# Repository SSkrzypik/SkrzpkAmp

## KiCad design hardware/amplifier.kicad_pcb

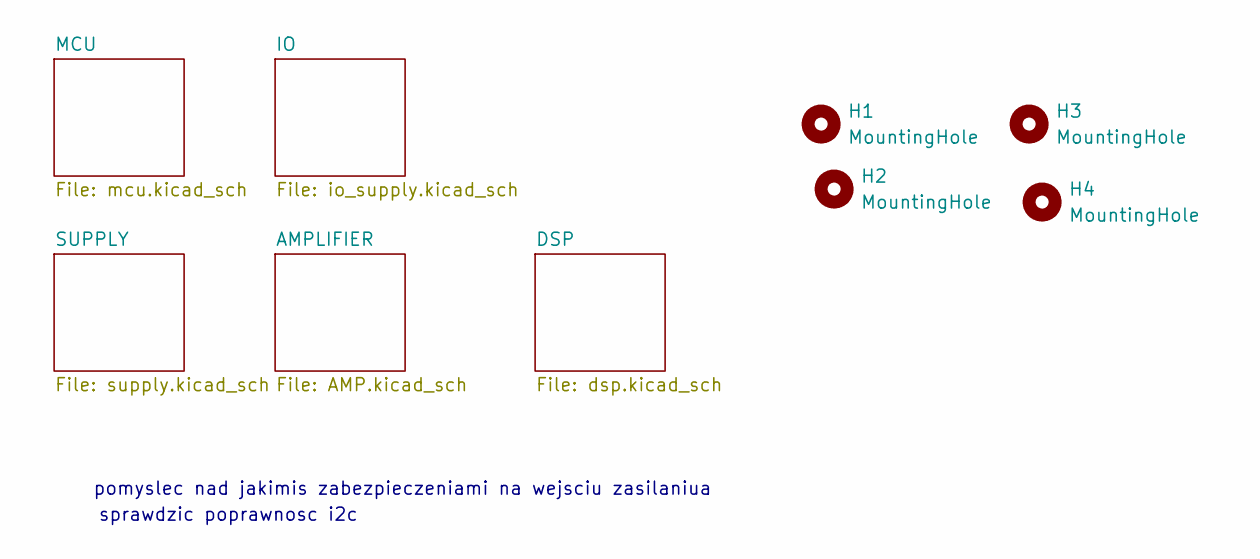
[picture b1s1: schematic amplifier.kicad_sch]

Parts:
H1, H2, H3, H4: MountingHole; MountingHole_3.2mm_M3

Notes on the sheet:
sprawdzic poprawnosc i2c
pomyslec nad jakimis zabezpieczeniami na wejsciu zasilaniua

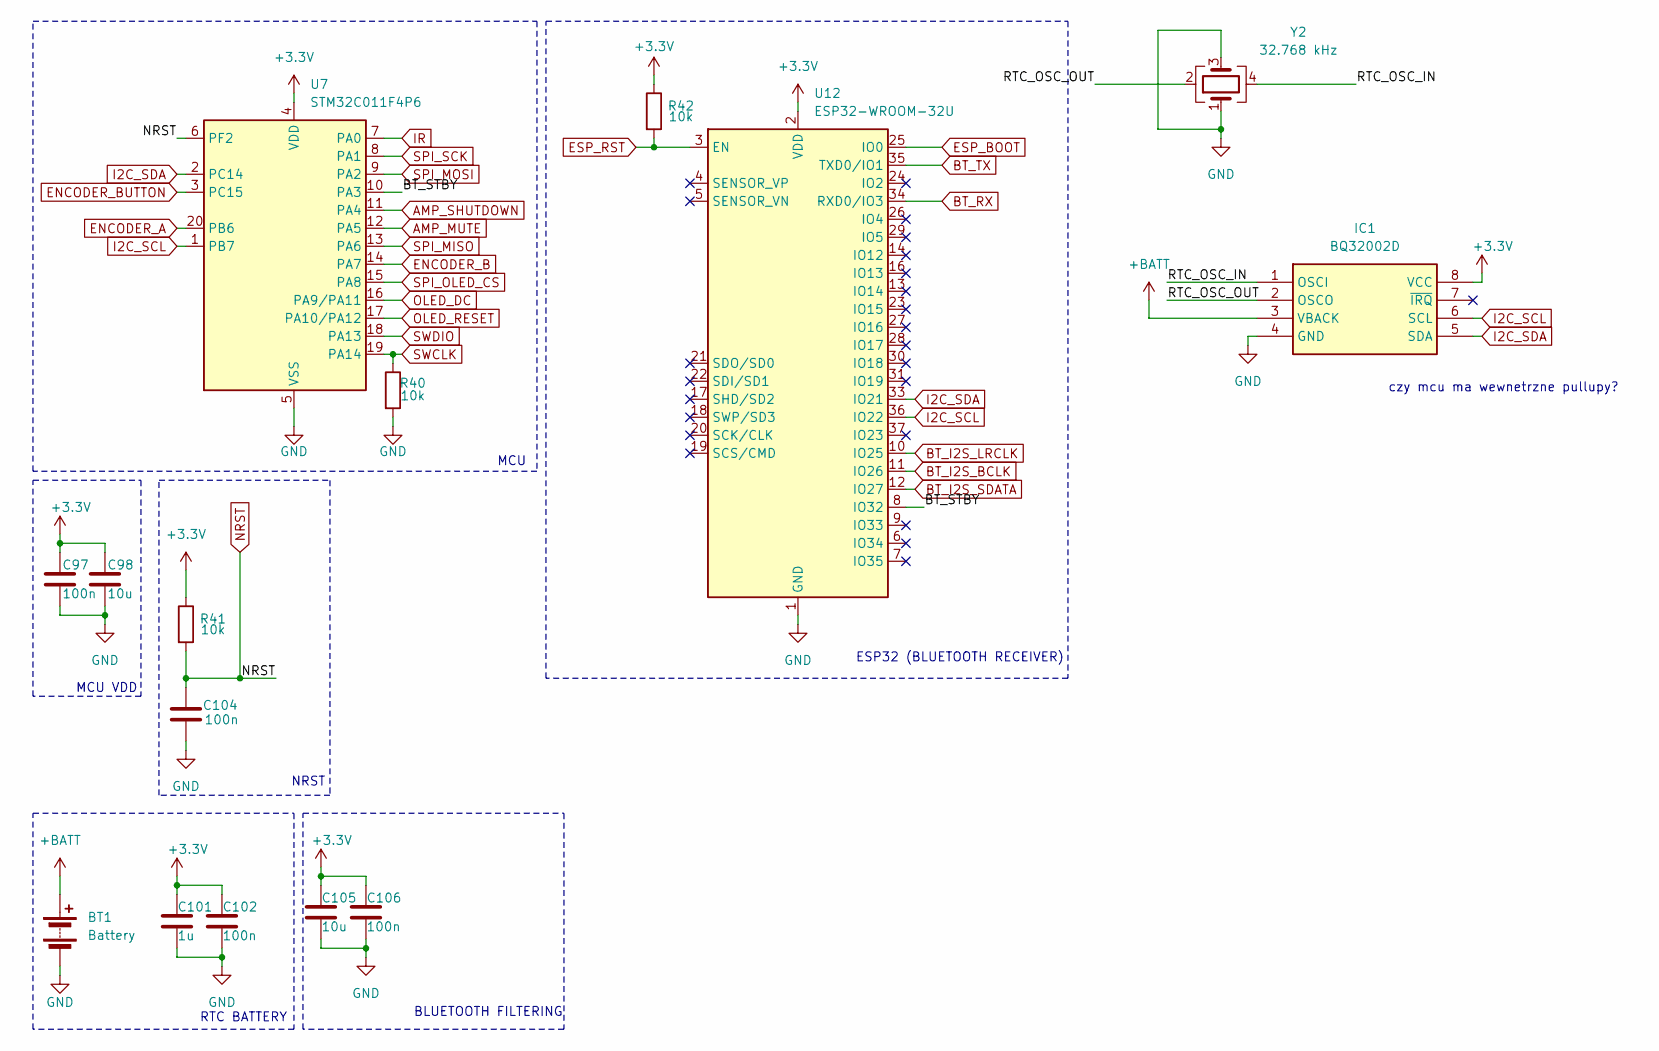
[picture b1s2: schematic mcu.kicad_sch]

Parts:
BT1: Battery; BatteryHolder_LINX_BAT-HLD-012-SMT
C97, C102, C104, C106: 100n; C_0603_1608Metric_Pad1.08x0.95mm_HandSolder
C98, C105: 10u; C_0603_1608Metric_Pad1.08x0.95mm_HandSolder
C101: 1u; C_0603_1608Metric_Pad1.08x0.95mm_HandSolder
IC1: BQ32002D; Mouser Part Number 595-BQ32002D
R40, R41, R42: 10k; R_0603_1608Metric_Pad0.98x0.95mm_HandSolder
U7: STM32C011F4P6; TSSOP-20_4.4x6.5mm_P0.65mm
U12: ESP32-WROOM-32U
Y2: 32.768 kHz; 32768K125PIMC306

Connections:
+BATT: BT1.1 (+), IC1.3 (VBACK)
/MCU/BT_STBY: U7.10 (PA3), U12.8 (IO32)
/MCU/RTC_OSC_IN: IC1.1 (OSCI), Y2.4
/MCU/RTC_OSC_OUT: IC1.2 (OSCO), Y2.2
AMP_MUTE: U7.12 (PA5); also elsewhere on the board
AMP_SHUTDOWN: U7.11 (PA4); also elsewhere on the board
BT_I2S_BCLK: U12.11 (IO26); also elsewhere on the board
BT_I2S_LRCLK: U12.10 (IO25); also elsewhere on the board
BT_I2S_SDATA: U12.12 (IO27); also elsewhere on the board
BT_RX: U12.34 (RXD0/IO3); also elsewhere on the board
BT_TX: U12.35 (TXD0/IO1); also elsewhere on the board
ENCODER_A: U7.20 (PB6); also elsewhere on the board
ENCODER_B: U7.14 (PA7); also elsewhere on the board
ENCODER_BUTTON: U7.3 (PC15); also elsewhere on the board
ESP_BOOT: U12.25 (IO0); also elsewhere on the board
ESP_RST: R42.2, U12.3 (EN); also elsewhere on the board
I2C_SCL: IC1.6 (SCL), U7.1 (PB7), U12.36 (IO22); also elsewhere on the board
I2C_SDA: IC1.5 (SDA), U7.2 (PC14), U12.33 (IO21); also elsewhere on the board
IR: U7.7 (PA0); also elsewhere on the board
NRST: C104.1, R41.2, U7.6 (PF2); also elsewhere on the board
OLED_DC: U7.16 (PA9/PA11); also elsewhere on the board
OLED_RESET: U7.17 (PA10/PA12); also elsewhere on the board
SPI_MISO: U7.13 (PA6); also elsewhere on the board
SPI_MOSI: U7.9 (PA2); also elsewhere on the board
SPI_OLED_CS: U7.15 (PA8); also elsewhere on the board
SPI_SCK: U7.8 (PA1); also elsewhere on the board
SWCLK: R40.1, U7.19 (PA14); also elsewhere on the board
SWDIO: U7.18 (PA13); also elsewhere on the board

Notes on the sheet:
MCU
ESP32 (BLUETOOTH RECEIVER)
czy mcu ma wewnetrzne pullupy?
RTC BATTERY
NRST
MCU VDD
BLUETOOTH FILTERING

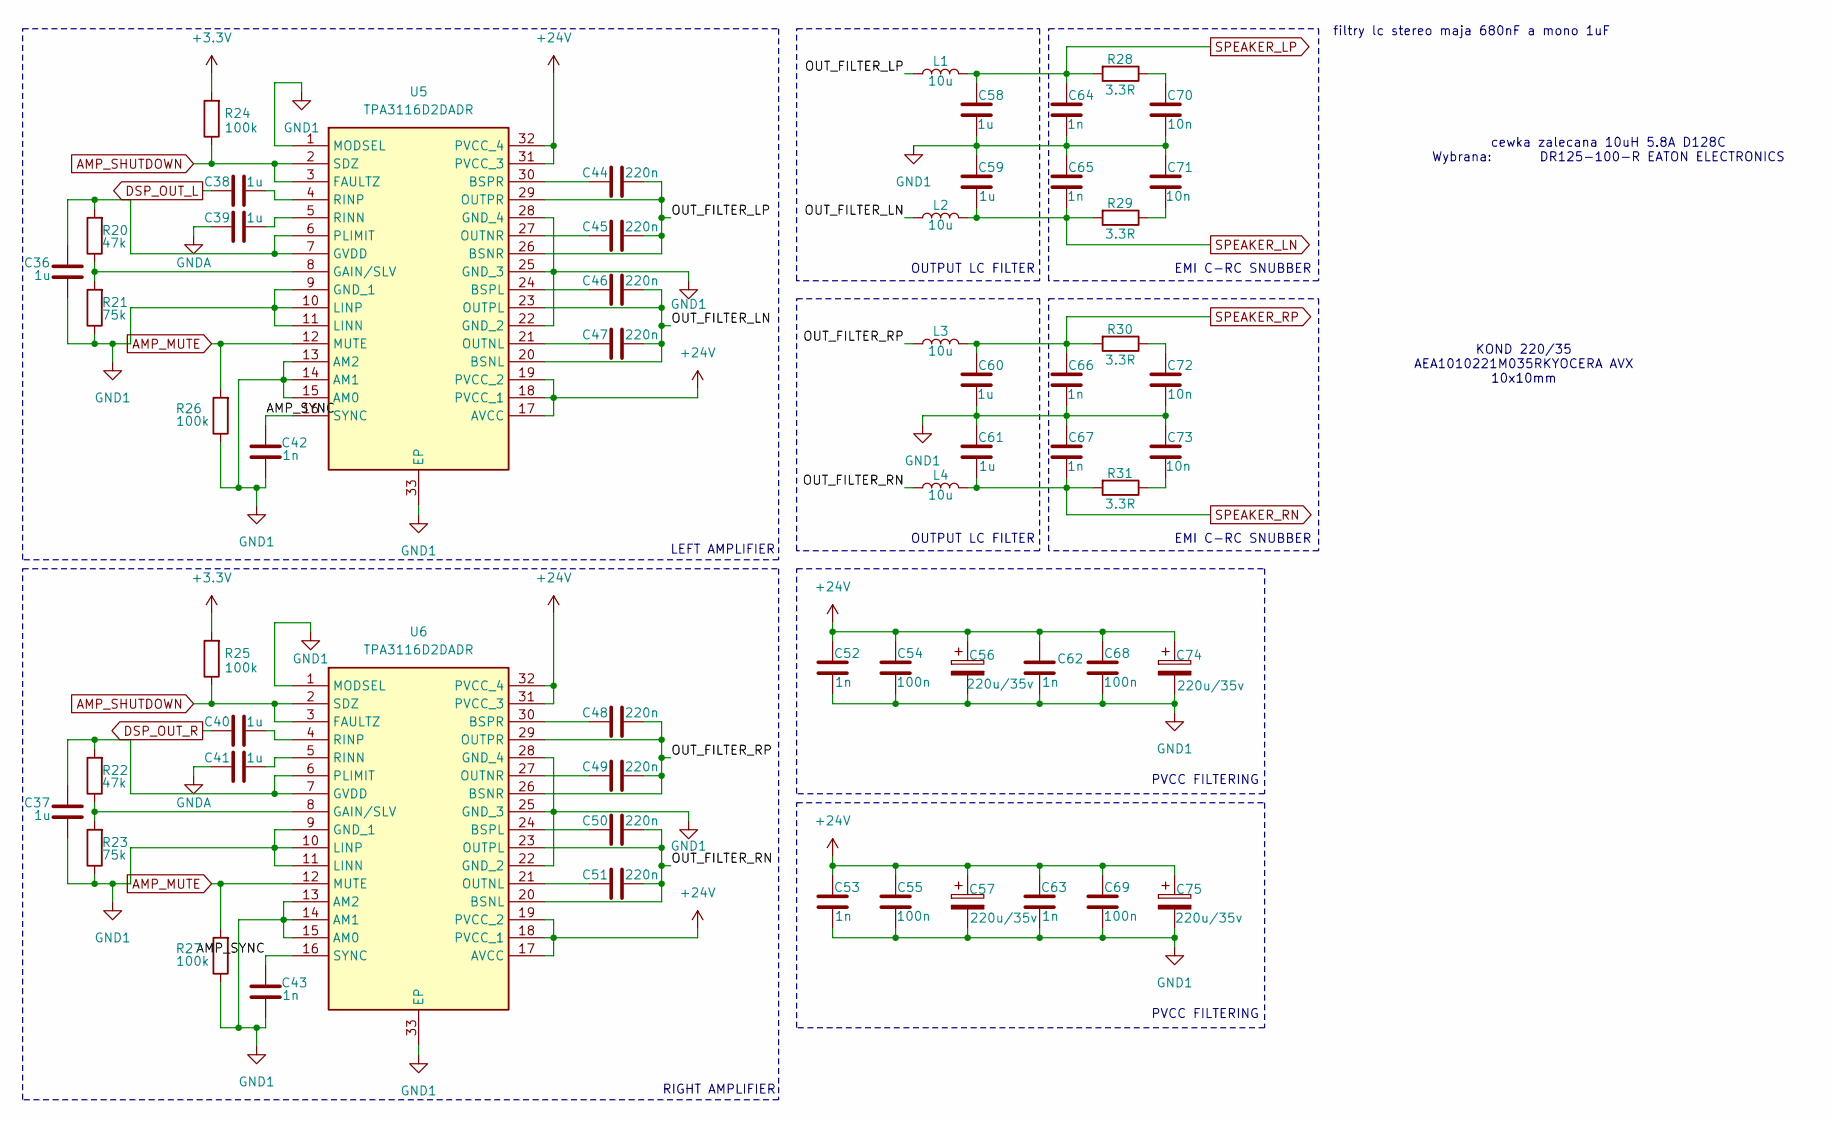
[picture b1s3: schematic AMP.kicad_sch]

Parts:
C36, C37, C38, C39, C40, C41, C58, C59, C60, C61: 1u; C_0603_1608Metric_Pad1.08x0.95mm_HandSolder
C42, C43, C52, C53, C62, C63, C64, C65, C66, C67: 1n; C_0603_1608Metric_Pad1.08x0.95mm_HandSolder
C44, C45, C46, C47, C48, C49, C50, C51: 220n; C_0603_1608Metric_Pad1.08x0.95mm_HandSolder
C54, C55, C68, C69: 100n; C_0603_1608Metric_Pad1.08x0.95mm_HandSolder
C56, C57, C74, C75: 220u/35v; CP_Elec_10x10
C70, C71, C72, C73: 10n; C_0603_1608Metric_Pad1.08x0.95mm_HandSolder
L1, L2, L3, L4: 10u; DR127-100-R
R20, R22: 47k; R_0603_1608Metric_Pad0.98x0.95mm_HandSolder
R21, R23: 75k; R_0603_1608Metric_Pad0.98x0.95mm_HandSolder
R24, R25, R26, R27: 100k; R_0603_1608Metric_Pad0.98x0.95mm_HandSolder
R28, R29, R30, R31: 3.3R; R_0603_1608Metric_Pad0.98x0.95mm_HandSolder
U5, U6: TPA3116D2DADR; SOP65P810X120-33N; Manufacturer_Part_Number TPA3116D2DADR

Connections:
/AMPLIFIER/AMP_SYNC: C42.1, C43.1, U5.16 (SYNC), U6.16 (SYNC)
/AMPLIFIER/OUT_FILTER_LN: C46.1, C47.1, L2.1, U5.20 (BSNL), U5.23 (OUTPL)
/AMPLIFIER/OUT_FILTER_LP: C44.1, C45.1, L1.1, U5.26 (BSNR), U5.29 (OUTPR)
/AMPLIFIER/OUT_FILTER_RN: C50.1, C51.1, L4.1, U6.20 (BSNL), U6.23 (OUTPL)
/AMPLIFIER/OUT_FILTER_RP: C48.1, C49.1, L3.1, U6.26 (BSNR), U6.29 (OUTPR)
AMP_MUTE: R26.2, R27.2, U5.12 (MUTE), U6.12 (MUTE); also elsewhere on the board
AMP_SHUTDOWN: R24.1, R25.1, U5.2 (SDZ), U5.3 (FAULTZ), U6.2 (SDZ), U6.3 (FAULTZ); also elsewhere on the board
DSP_OUT_L: C38.2; also elsewhere on the board
DSP_OUT_R: C40.2; also elsewhere on the board
GND1: C36.2, C37.2, C42.2, C43.2, C52.2, C53.2, C54.2, C55.2, C56.2, C57.2, C58.2, C59.1, C60.2, C61.1, C62.2, C63.2, C64.2, C65.1, C66.2, C67.1, C68.2, C69.2, C70.2, C71.1, C72.2, C73.1, C74.2, C75.2, R21.1, R23.1, R26.1, R27.1, U5.1 (MODSEL), U5.9 (GND_1), U5.10 (LINP), U5.11 (LINN), U5.13 (AM2), U5.14 (AM1), U5.15 (AM0), U5.22 (GND_2), U5.25 (GND_3), U5.28 (GND_4), U5.33 (EP), U6.1 (MODSEL), U6.9 (GND_1), U6.10 (LINP), U6.11 (LINN), U6.13 (AM2), U6.14 (AM1), U6.15 (AM0), U6.22 (GND_2), U6.25 (GND_3), U6.28 (GND_4), U6.33 (EP); also elsewhere on the board
unnamed: C70.1, R28.1
unnamed: C71.2, R29.1
unnamed: C72.1, R30.1
unnamed: C73.2, R31.1
unnamed: C46.2, U5.24 (BSPL)
unnamed: C44.2, U5.30 (BSPR)
unnamed: R20.1, R21.2, U5.8 (GAIN/SLV)
unnamed: C36.1, R20.2, U5.6 (PLIMIT), U5.7 (GVDD)
unnamed: C47.2, U5.21 (OUTNL)
unnamed: C45.2, U5.27 (OUTNR)
unnamed: C39.1, U5.5 (RINN)
unnamed: C38.1, U5.4 (RINP)
unnamed: C50.2, U6.24 (BSPL)
unnamed: C48.2, U6.30 (BSPR)
unnamed: R22.1, R23.2, U6.8 (GAIN/SLV)
unnamed: C37.1, R22.2, U6.6 (PLIMIT), U6.7 (GVDD)
unnamed: C51.2, U6.21 (OUTNL)
unnamed: C49.2, U6.27 (OUTNR)
unnamed: C41.1, U6.5 (RINN)
unnamed: C40.1, U6.4 (RINP)
SPEAKER_LN: C59.2, C65.2, L2.2, R29.2; also elsewhere on the board
SPEAKER_LP: C58.1, C64.1, L1.2, R28.2; also elsewhere on the board
SPEAKER_RN: C61.2, C67.2, L4.2, R31.2; also elsewhere on the board
SPEAKER_RP: C60.1, C66.1, L3.2, R30.2; also elsewhere on the board

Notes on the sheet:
PVCC FILTERING
EMI C-RC SNUBBER
RIGHT AMPLIFIER
filtry lc stereo maja 680nF a mono 1uF
OUTPUT LC FILTER
cewka zalecana 10uH 5.8A D128C Wybrana: DR125-100-R EATON ELECTRONICS
LEFT AMPLIFIER
KOND 220/35 AEA1010221M035RKYOCERA AVX 10x10mm

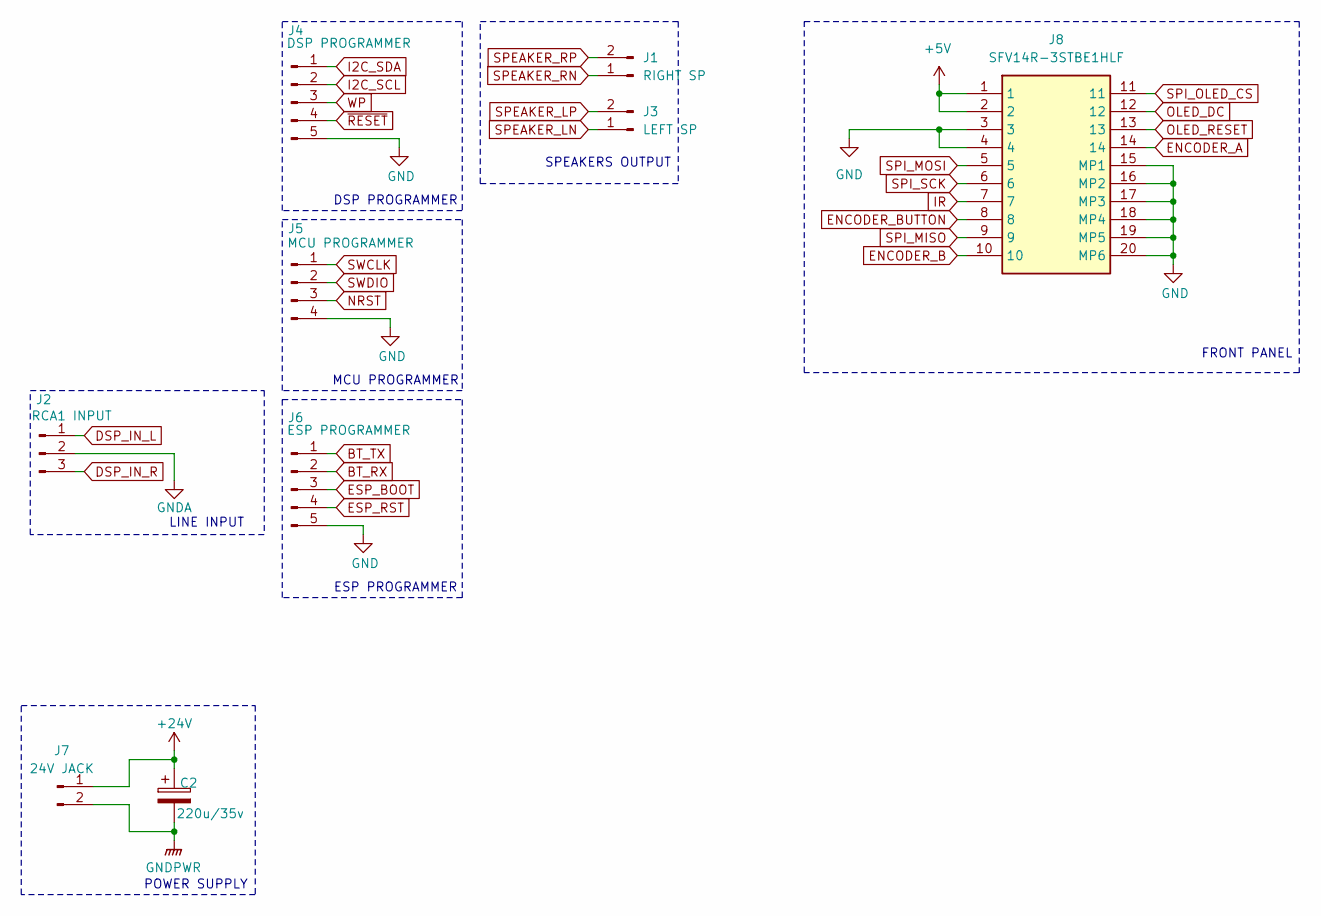
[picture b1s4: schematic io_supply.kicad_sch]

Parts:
C2: 220u/35v; CP_Elec_10x10
J1: RIGHT SP; 2828362
J2: RCA1 INPUT; JST_PH_B3B-PH-K_1x03_P2.00mm_Vertical
J3: LEFT SP; 2828362
J4: DSP PROGRAMMER; PinHeader_1x05_P2.54mm_Vertical
J5: MCU PROGRAMMER; PinHeader_1x04_P2.54mm_Vertical
J6: ESP PROGRAMMER; PinHeader_1x05_P2.54mm_Vertical
J7: 24V JACK; 2828362
J8: SFV14R-3STBE1HLF; SFV14R3STBE1HLF; Manufacturer_Part_Number SFV14R-3STBE1HLF

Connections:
BT_RX: J6.2; also elsewhere on the board
BT_TX: J6.1; also elsewhere on the board
DSP_IN_R: J2.3; also elsewhere on the board
ENCODER_A: J8.14; also elsewhere on the board
ENCODER_B: J8.10; also elsewhere on the board
ENCODER_BUTTON: J8.8; also elsewhere on the board
ESP_BOOT: J6.3; also elsewhere on the board
ESP_RST: J6.4; also elsewhere on the board
I2C_SCL: J4.2; also elsewhere on the board
I2C_SDA: J4.1; also elsewhere on the board
IR: J8.7; also elsewhere on the board
NRST: J5.3; also elsewhere on the board
OLED_DC: J8.12; also elsewhere on the board
OLED_RESET: J8.13; also elsewhere on the board
SPEAKER_LN: J3.1; also elsewhere on the board
SPEAKER_LP: J3.2; also elsewhere on the board
SPEAKER_RN: J1.1; also elsewhere on the board
SPEAKER_RP: J1.2; also elsewhere on the board
SPI_MISO: J8.9; also elsewhere on the board
SPI_MOSI: J8.5; also elsewhere on the board
SPI_OLED_CS: J8.11; also elsewhere on the board
SPI_SCK: J8.6; also elsewhere on the board
SWCLK: J5.1; also elsewhere on the board
SWDIO: J5.2; also elsewhere on the board
WP: J4.3; also elsewhere on the board
~RESET: J4.4; also elsewhere on the board

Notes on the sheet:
POWER SUPPLY
MCU PROGRAMMER
DSP PROGRAMMER
FRONT PANEL
SPEAKERS OUTPUT
LINE INPUT
ESP PROGRAMMER

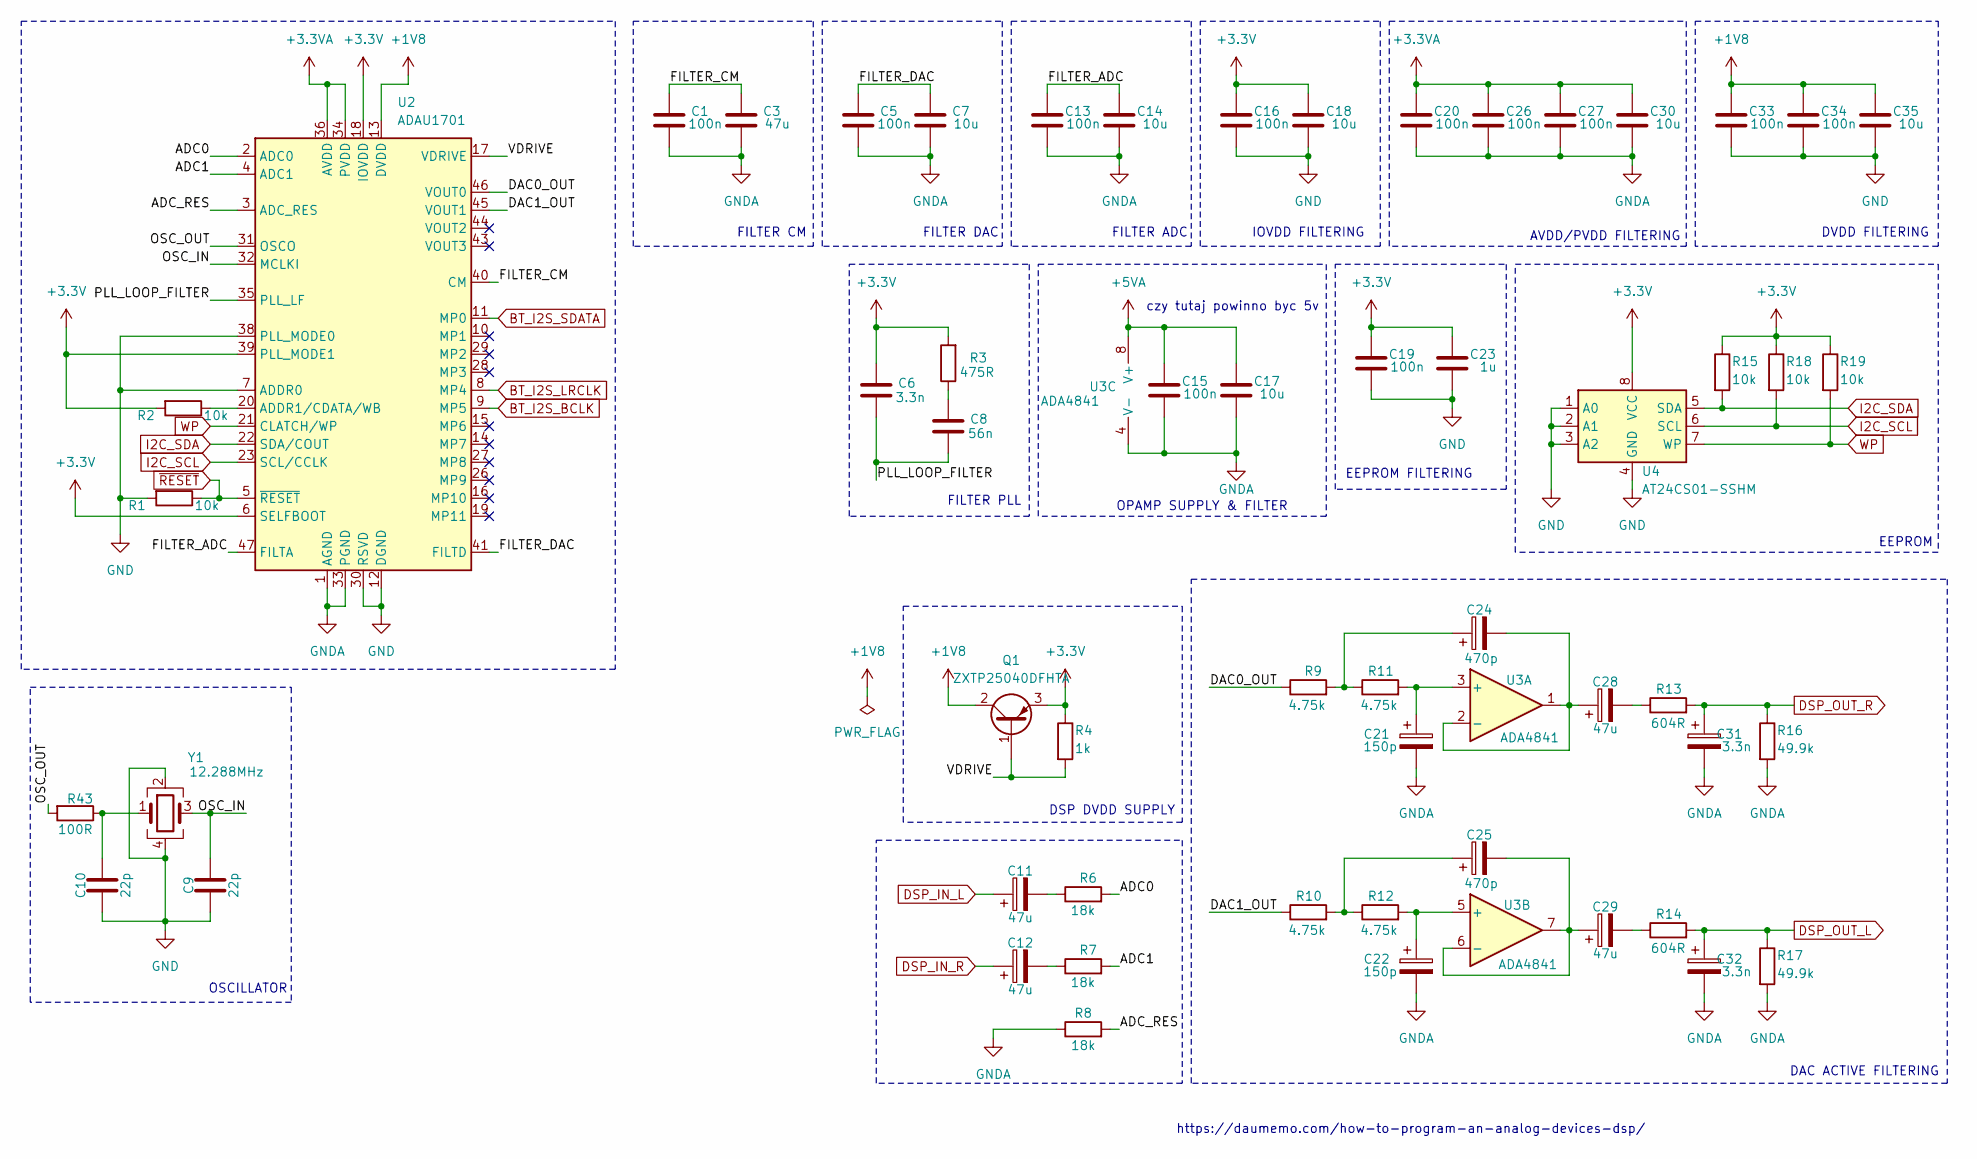
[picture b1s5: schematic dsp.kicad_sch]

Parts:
C1, C5, C13, C15, C16, C19, C20, C26, C27, C33, C34: 100n; C_0603_1608Metric_Pad1.08x0.95mm_HandSolder
C3, C11, C12, C28, C29: 47u; C_0603_1608Metric_Pad1.08x0.95mm_HandSolder
C6, C31, C32: 3.3n; C_0603_1608Metric_Pad1.08x0.95mm_HandSolder
C7, C14, C17, C18, C30, C35: 10u; C_0603_1608Metric_Pad1.08x0.95mm_HandSolder
C8: 56n; C_0603_1608Metric_Pad1.08x0.95mm_HandSolder
C9, C10: 22p; C_0603_1608Metric_Pad1.08x0.95mm_HandSolder
C21, C22: 150p; C_0603_1608Metric_Pad1.08x0.95mm_HandSolder
C23: 1u; C_0603_1608Metric_Pad1.08x0.95mm_HandSolder
C24, C25: 470p; C_0603_1608Metric_Pad1.08x0.95mm_HandSolder
Q1: ZXTP25040DFHTA; SOT-23
R1, R2, R15, R18, R19: 10k; R_0603_1608Metric_Pad0.98x0.95mm_HandSolder
R3: 475R; R_0603_1608Metric_Pad0.98x0.95mm_HandSolder
R4: 1k; R_0603_1608Metric_Pad0.98x0.95mm_HandSolder
R6, R7, R8: 18k; R_0603_1608Metric_Pad0.98x0.95mm_HandSolder
R9, R10, R11, R12: 4.75k; R_0603_1608Metric_Pad0.98x0.95mm_HandSolder
R13, R14: 604R; R_0603_1608Metric_Pad0.98x0.95mm_HandSolder
R16, R17: 49.9k; R_0603_1608Metric_Pad0.98x0.95mm_HandSolder
R43: 100R; R_0603_1608Metric_Pad0.98x0.95mm_HandSolder
U2: ADAU1701; LQFP-48_7x7mm_P0.5mm
U3: ADA4841; MSOP-8_3x3mm_P0.65mm
U4: AT24CS01-SSHM; SOIC127P600X175-8N
Y1: 12.288MHz; ABM3B

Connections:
+1V8: C33.1, C34.1, C35.1, Q1.2 (C), U2.13 (DVDD), U2.24 (DVDD)
/DSP/ADC0: R6.2, U2.2 (ADC0)
/DSP/ADC1: R7.2, U2.4 (ADC1)
/DSP/ADC_RES: R8.2, U2.3 (ADC_RES)
/DSP/DAC0_OUT: R9.1, U2.46 (VOUT0)
/DSP/DAC1_OUT: R10.1, U2.45 (VOUT1)
/DSP/FILTER_ADC: C13.1, C14.1, U2.47 (FILTA)
/DSP/OSC_OUT: R43.2, U2.31 (OSCO)
/DSP/VDRIVE: Q1.1 (B), R4.2, U2.17 (VDRIVE)
BT_I2S_BCLK: U2.9 (MP5); also elsewhere on the board
BT_I2S_LRCLK: U2.8 (MP4); also elsewhere on the board
BT_I2S_SDATA: U2.11 (MP0); also elsewhere on the board
DSP_IN_R: C12.1; also elsewhere on the board
DSP_OUT_L: C32.1, R14.2, R17.1; also elsewhere on the board
DSP_OUT_R: C31.1, R13.2, R16.1; also elsewhere on the board
I2C_SCL: R18.2, U2.23 (SCL/CCLK), U4.6 (SCL); also elsewhere on the board
I2C_SDA: R15.2, U2.22 (SDA/COUT), U4.5 (SDA); also elsewhere on the board
unnamed: C12.2, R7.1
unnamed: C24.1, R9.2, R11.1
unnamed: C25.1, R10.2, R12.1
unnamed: C28.2, R13.1
unnamed: C29.2, R14.1
unnamed: R2.1, U2.20 (ADDR1/CDATA/WB)
unnamed: C21.1, R11.2, U3.3 (+)
unnamed: C24.2, C28.1, U3.1, U3.2 (-)
unnamed: C22.1, R12.2, U3.5 (+)
unnamed: C25.2, C29.1, U3.6 (-), U3.7
WP: R19.2, U2.21 (CLATCH/WP), U4.7 (WP); also elsewhere on the board
~RESET: R1.1, U2.5 (~RESET); also elsewhere on the board

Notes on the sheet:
EEPROM
DAC ACTIVE FILTERING
AVDD/PVDD FILTERING
FILTER PLL
DVDD FILTERING
https://daumemo.com/how-to-program-an-analog-devices-dsp/
FILTER DAC
OPAMP SUPPLY & FILTER
czy tutaj powinno byc 5v
EEPROM FILTERING
FILTER ADC
FILTER CM
OSCILLATOR
IOVDD FILTERING
DSP DVDD SUPPLY

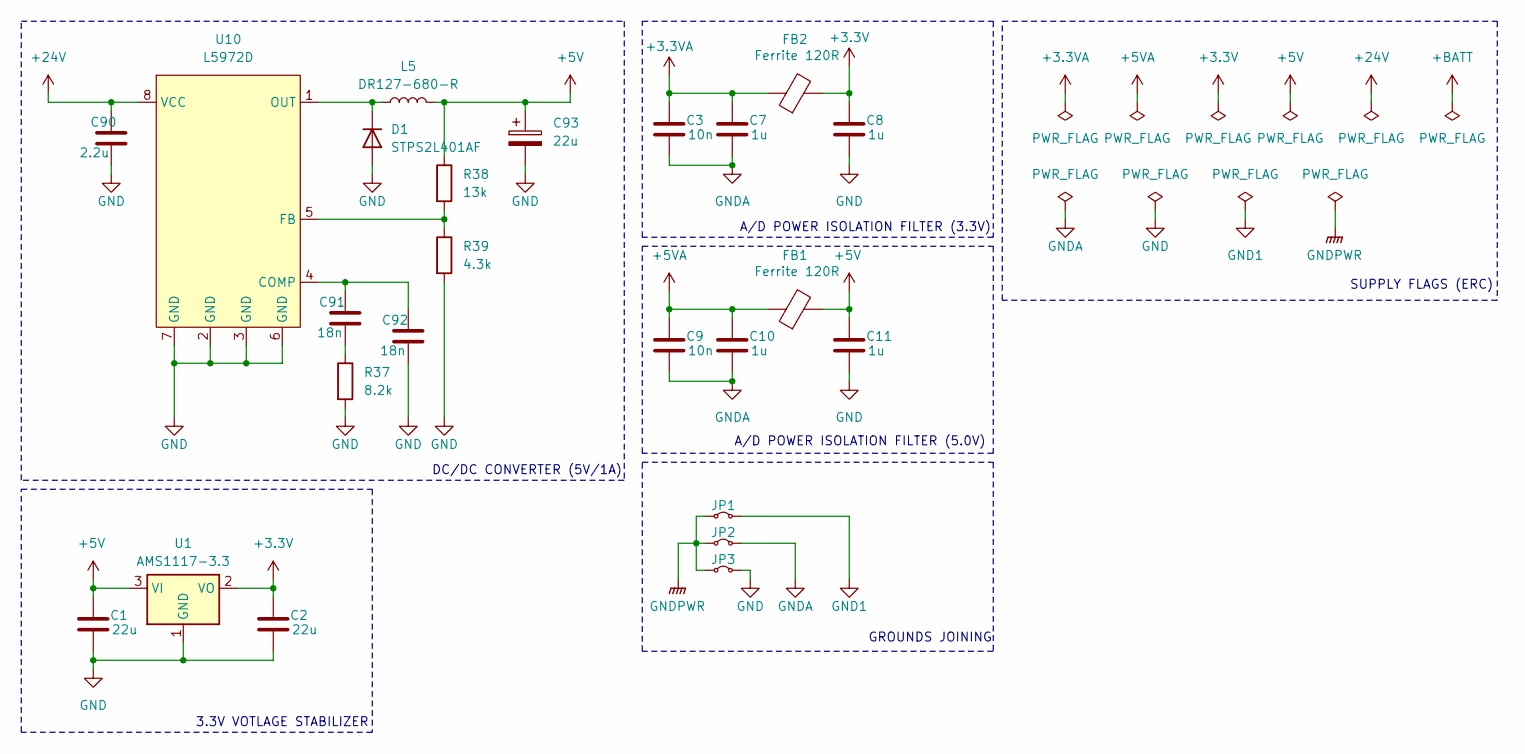
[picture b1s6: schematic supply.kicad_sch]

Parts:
C1, C2, C93: 22u; C_0603_1608Metric_Pad1.08x0.95mm_HandSolder
C3, C9: 10n; C_0603_1608Metric_Pad1.08x0.95mm_HandSolder
C7, C8, C10, C11: 1u; C_0603_1608Metric_Pad1.08x0.95mm_HandSolder
C90: 2.2u; C_0603_1608Metric_Pad1.08x0.95mm_HandSolder
C91, C92: 18n; C_0603_1608Metric_Pad1.08x0.95mm_HandSolder
D1: STPS2L401AF; STPS2L40AF
FB1, FB2: Ferrite 120R; L_0805_2012Metric_Pad1.05x1.20mm_HandSolder
JP1, JP2, JP3: Jumper_2_Small_Bridged; R_1210_3225Metric_Pad1.30x2.65mm_HandSolder
L5: DR127-680-R; DR127-100-R
R37: 8.2k; R_0603_1608Metric_Pad0.98x0.95mm_HandSolder
R38: 13k; R_0603_1608Metric_Pad0.98x0.95mm_HandSolder
R39: 4.3k; R_0603_1608Metric_Pad0.98x0.95mm_HandSolder
U1: AMS1117-3.3; SOT-223-3_TabPin2
U10: L5972D; SO-8_3.9x4.9mm_P1.27mm

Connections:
GND1: JP1.2 (B); also elsewhere on the board
unnamed: C91.2, R37.1
unnamed: D1.1 (K), L5.1, U10.1 (OUT)
unnamed: C91.1, C92.1, U10.4 (COMP)
unnamed: R38.2, R39.1, U10.5 (FB)

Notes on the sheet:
SUPPLY FLAGS (ERC)
A/D POWER ISOLATION FILTER (5.0V)
DC/DC CONVERTER (5V/1A)
A/D POWER ISOLATION FILTER (3.3V)
GROUNDS JOINING
3.3V VOTLAGE STABILIZER

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
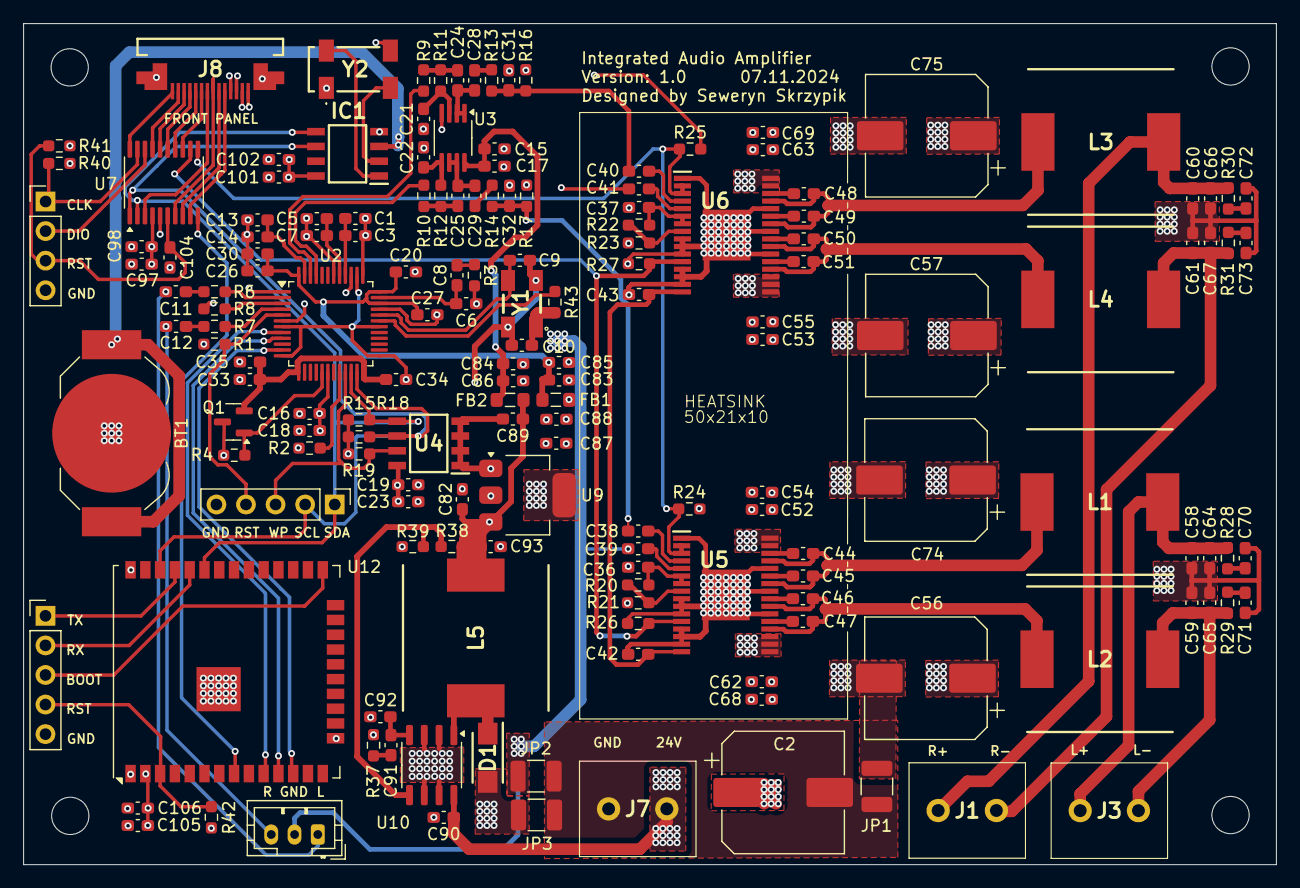
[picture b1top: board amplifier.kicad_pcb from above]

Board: 4 copper layers, 107.6 x 72.2 mm, 167 parts (0 on the bottom side), 102 nets.

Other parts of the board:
C82, C87: 22u; C_0603_1608Metric_Pad1.08x0.95mm_HandSolder
C83, C84: 10n; C_0603_1608Metric_Pad1.08x0.95mm_HandSolder
C85, C86, C88, C89: 1u; C_0603_1608Metric_Pad1.08x0.95mm_HandSolder
U9: AMS1117-3.3; SOT-223-3_TabPin2
